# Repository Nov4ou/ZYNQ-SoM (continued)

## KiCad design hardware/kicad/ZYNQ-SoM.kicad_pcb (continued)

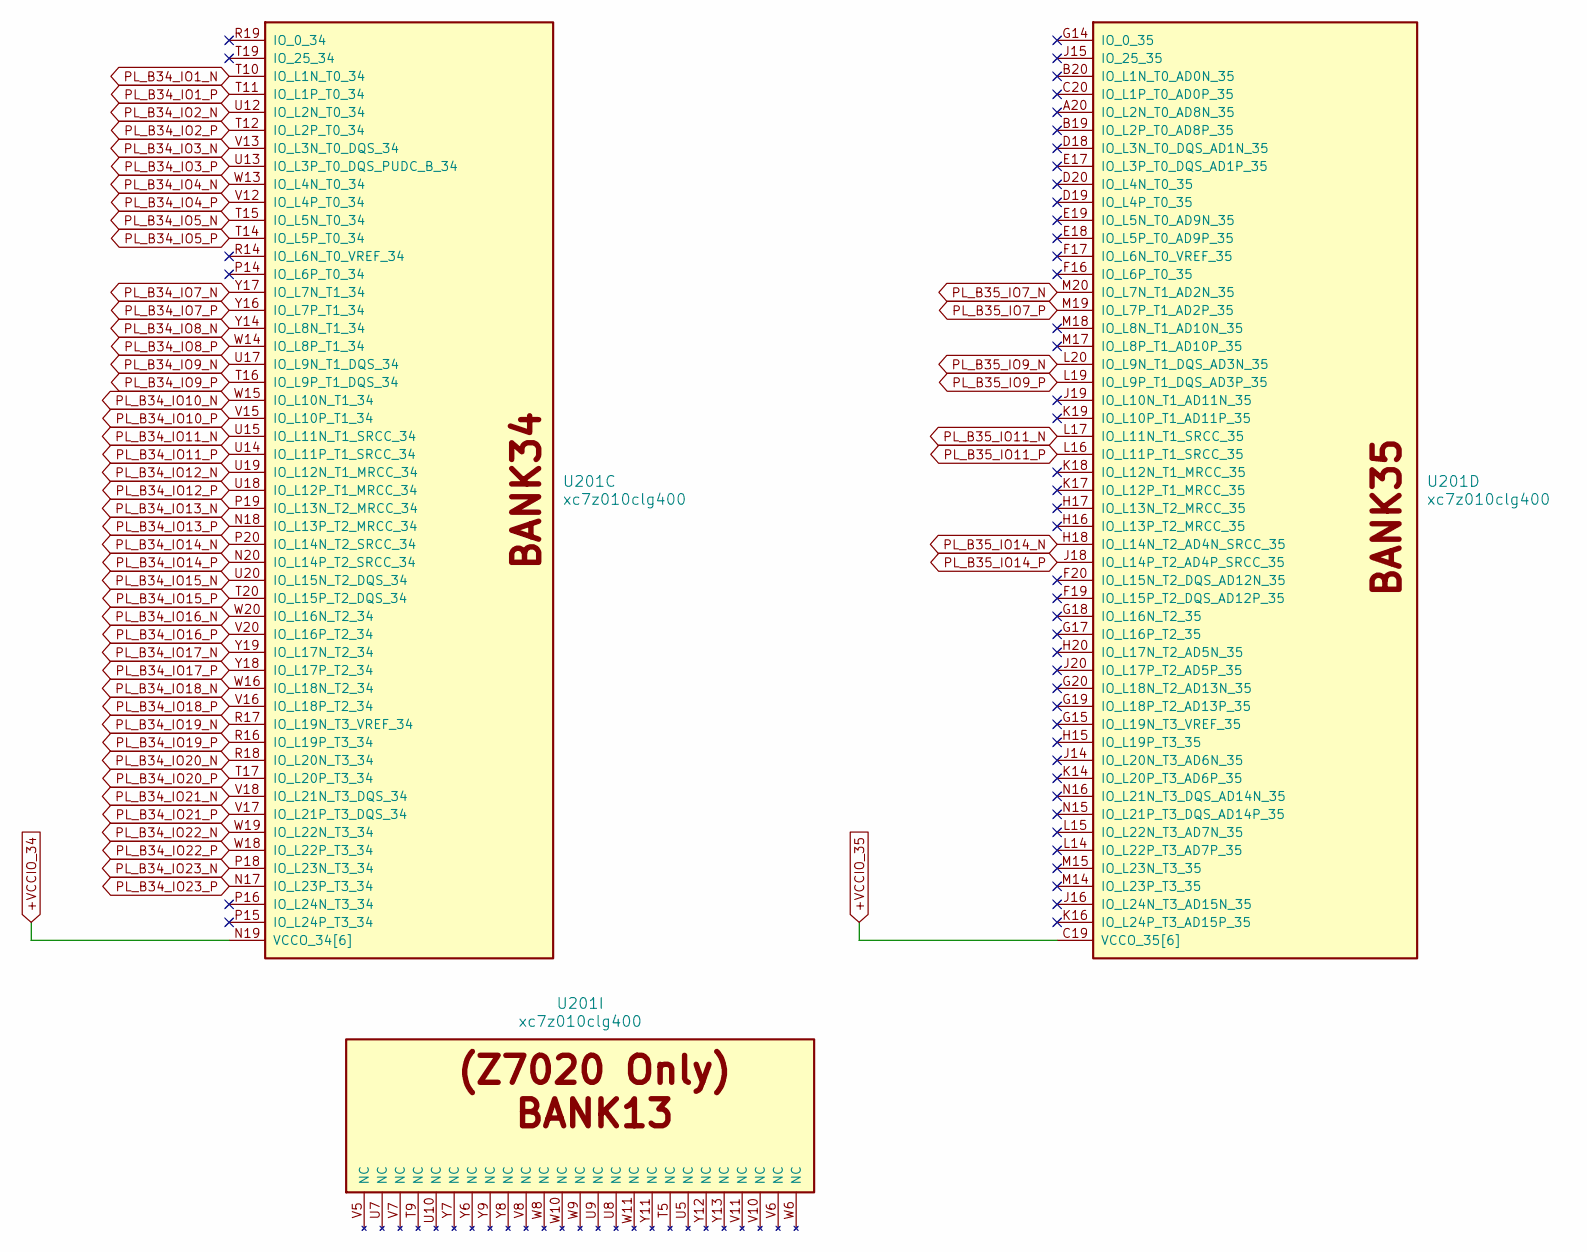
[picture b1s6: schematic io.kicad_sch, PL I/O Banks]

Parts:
U201: xc7z010clg400; Xilinx_CLG400

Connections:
+VCCIO_34: U201.N19 (VCCO_34[6]), U201.R15 (VCCO_34[6]), U201.T18 (VCCO_34[6]), U201.V14 (VCCO_34[6]), U201.W17 (VCCO_34[6]), U201.Y20 (VCCO_34[6]); also elsewhere on the board
+VCCIO_35: U201.C19 (VCCO_35[6]), U201.F18 (VCCO_35[6]), U201.H14 (VCCO_35[6]), U201.J17 (VCCO_35[6]), U201.K20 (VCCO_35[6]), U201.M16 (VCCO_35[6]); also elsewhere on the board
PL_B34_IO1_N: U201.T10 (IO_L1N_T0_34); also elsewhere on the board
PL_B34_IO1_P: U201.T11 (IO_L1P_T0_34); also elsewhere on the board
PL_B34_IO2_N: U201.U12 (IO_L2N_T0_34); also elsewhere on the board
PL_B34_IO2_P: U201.T12 (IO_L2P_T0_34); also elsewhere on the board
PL_B34_IO3_N: U201.V13 (IO_L3N_T0_DQS_34); also elsewhere on the board
PL_B34_IO3_P: U201.U13 (IO_L3P_T0_DQS_PUDC_B_34); also elsewhere on the board
PL_B34_IO4_N: U201.W13 (IO_L4N_T0_34); also elsewhere on the board
PL_B34_IO4_P: U201.V12 (IO_L4P_T0_34); also elsewhere on the board
PL_B34_IO5_N: U201.T15 (IO_L5N_T0_34); also elsewhere on the board
PL_B34_IO5_P: U201.T14 (IO_L5P_T0_34); also elsewhere on the board
PL_B34_IO7_N: U201.Y17 (IO_L7N_T1_34); also elsewhere on the board
PL_B34_IO7_P: U201.Y16 (IO_L7P_T1_34); also elsewhere on the board
PL_B34_IO8_N: U201.Y14 (IO_L8N_T1_34); also elsewhere on the board
PL_B34_IO8_P: U201.W14 (IO_L8P_T1_34); also elsewhere on the board
PL_B34_IO9_N: U201.U17 (IO_L9N_T1_DQS_34); also elsewhere on the board
PL_B34_IO9_P: U201.T16 (IO_L9P_T1_DQS_34); also elsewhere on the board
PL_B34_IO10_N: U201.W15 (IO_L10N_T1_34); also elsewhere on the board
PL_B34_IO10_P: U201.V15 (IO_L10P_T1_34); also elsewhere on the board
PL_B34_IO11_N: U201.U15 (IO_L11N_T1_SRCC_34); also elsewhere on the board
PL_B34_IO11_P: U201.U14 (IO_L11P_T1_SRCC_34); also elsewhere on the board
PL_B34_IO12_N: U201.U19 (IO_L12N_T1_MRCC_34); also elsewhere on the board
PL_B34_IO12_P: U201.U18 (IO_L12P_T1_MRCC_34); also elsewhere on the board
PL_B34_IO13_N: U201.P19 (IO_L13N_T2_MRCC_34); also elsewhere on the board
PL_B34_IO13_P: U201.N18 (IO_L13P_T2_MRCC_34); also elsewhere on the board
PL_B34_IO14_N: U201.P20 (IO_L14N_T2_SRCC_34); also elsewhere on the board
PL_B34_IO14_P: U201.N20 (IO_L14P_T2_SRCC_34); also elsewhere on the board
PL_B34_IO15_N: U201.U20 (IO_L15N_T2_DQS_34); also elsewhere on the board
PL_B34_IO15_P: U201.T20 (IO_L15P_T2_DQS_34); also elsewhere on the board
PL_B34_IO16_N: U201.W20 (IO_L16N_T2_34); also elsewhere on the board
PL_B34_IO16_P: U201.V20 (IO_L16P_T2_34); also elsewhere on the board
PL_B34_IO17_N: U201.Y19 (IO_L17N_T2_34); also elsewhere on the board
PL_B34_IO17_P: U201.Y18 (IO_L17P_T2_34); also elsewhere on the board
PL_B34_IO18_N: U201.W16 (IO_L18N_T2_34); also elsewhere on the board
PL_B34_IO18_P: U201.V16 (IO_L18P_T2_34); also elsewhere on the board
PL_B34_IO19_N: U201.R17 (IO_L19N_T3_VREF_34); also elsewhere on the board
PL_B34_IO19_P: U201.R16 (IO_L19P_T3_34); also elsewhere on the board
PL_B34_IO20_N: U201.R18 (IO_L20N_T3_34); also elsewhere on the board
PL_B34_IO20_P: U201.T17 (IO_L20P_T3_34); also elsewhere on the board
PL_B34_IO21_N: U201.V18 (IO_L21N_T3_DQS_34); also elsewhere on the board
PL_B34_IO21_P: U201.V17 (IO_L21P_T3_DQS_34); also elsewhere on the board
PL_B34_IO22_N: U201.W19 (IO_L22N_T3_34); also elsewhere on the board
PL_B34_IO22_P: U201.W18 (IO_L22P_T3_34); also elsewhere on the board
PL_B34_IO23_N: U201.P18 (IO_L23N_T3_34); also elsewhere on the board
PL_B34_IO23_P: U201.N17 (IO_L23P_T3_34); also elsewhere on the board
PL_B35_IO7_N: U201.M20 (IO_L7N_T1_AD2N_35); also elsewhere on the board
PL_B35_IO7_P: U201.M19 (IO_L7P_T1_AD2P_35); also elsewhere on the board
PL_B35_IO9_N: U201.L20 (IO_L9N_T1_DQS_AD3N_35); also elsewhere on the board
PL_B35_IO9_P: U201.L19 (IO_L9P_T1_DQS_AD3P_35); also elsewhere on the board
PL_B35_IO11_N: U201.L17 (IO_L11N_T1_SRCC_35); also elsewhere on the board
PL_B35_IO11_P: U201.L16 (IO_L11P_T1_SRCC_35); also elsewhere on the board
PL_B35_IO14_N: U201.H18 (IO_L14N_T2_AD4N_SRCC_35); also elsewhere on the board
PL_B35_IO14_P: U201.J18 (IO_L14P_T2_AD4P_SRCC_35); also elsewhere on the board

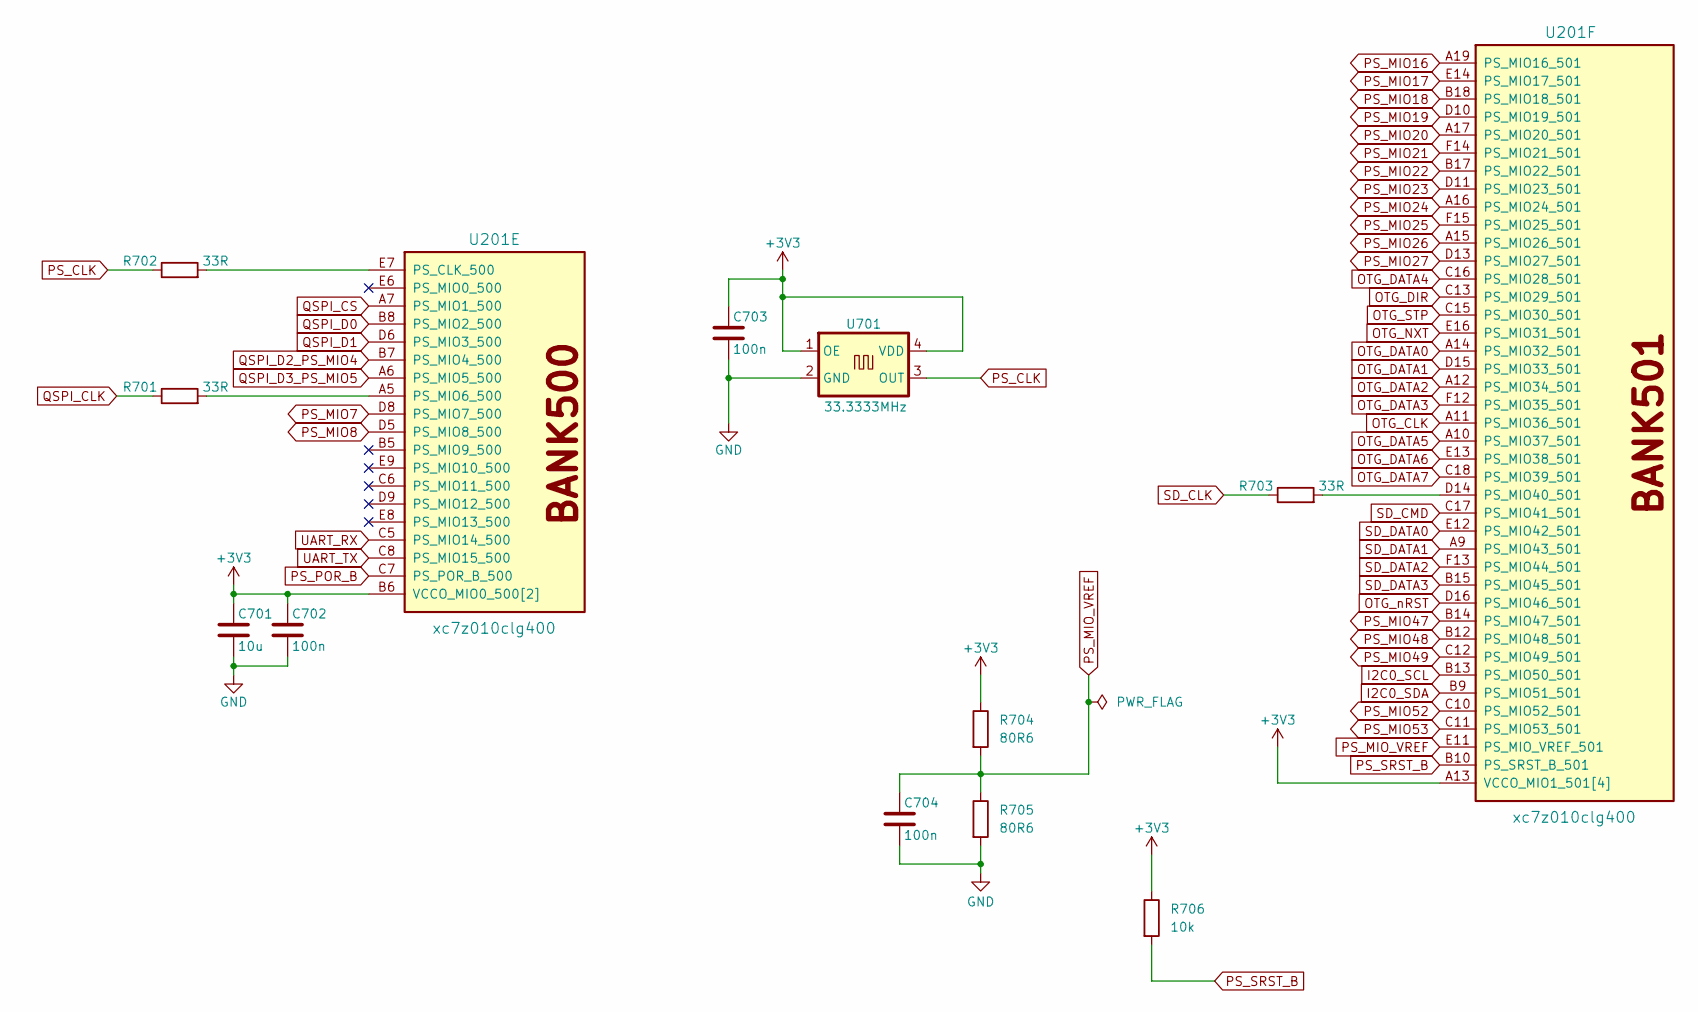
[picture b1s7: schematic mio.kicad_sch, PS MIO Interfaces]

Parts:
C701: 10u; C_0805_2012Metric
C702, C703, C704: 100n; C_0402_1005Metric
R701, R702, R703: 33R; R_0402_1005Metric
R704, R705: 80R6; R_0402_1005Metric
R706: 10k; R_0402_1005Metric
U201: xc7z010clg400; Xilinx_CLG400
U701: 33.3333MHz; Oscillator_SMD_SeikoEpson_SG8002CE-4Pin_3.2x2.5mm

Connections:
+3V3: C701.1, C702.1, C703.1, R704.1, R706.1, U201.A13 (VCCO_MIO1_501[4]), U201.B6 (VCCO_MIO0_500[2]), U201.B16 (VCCO_MIO1_501[4]), U201.D7 (VCCO_MIO0_500[2]), U201.D12 (VCCO_MIO1_501[4]), U201.E15 (VCCO_MIO1_501[4]), U701.1 (OE), U701.4 (VDD); also elsewhere on the board
GND: C701.2, C702.2, C703.2, C704.2, R705.2, U701.2 (GND); also elsewhere on the board
I2C0_SCL: U201.B13 (PS_MIO50_501); also elsewhere on the board
I2C0_SDA: U201.B9 (PS_MIO51_501); also elsewhere on the board
unnamed: R702.2, U201.E7 (PS_CLK_500)
unnamed: R701.2, U201.A5 (PS_MIO6_500)
unnamed: R703.2, U201.D14 (PS_MIO40_501)
OTG_CLK: U201.A11 (PS_MIO36_501); also elsewhere on the board
OTG_DATA0: U201.A14 (PS_MIO32_501); also elsewhere on the board
OTG_DATA1: U201.D15 (PS_MIO33_501); also elsewhere on the board
OTG_DATA2: U201.A12 (PS_MIO34_501); also elsewhere on the board
OTG_DATA3: U201.F12 (PS_MIO35_501); also elsewhere on the board
OTG_DATA4: U201.C16 (PS_MIO28_501); also elsewhere on the board
OTG_DATA5: U201.A10 (PS_MIO37_501); also elsewhere on the board
OTG_DATA6: U201.E13 (PS_MIO38_501); also elsewhere on the board
OTG_DATA7: U201.C18 (PS_MIO39_501); also elsewhere on the board
OTG_DIR: U201.C13 (PS_MIO29_501); also elsewhere on the board
OTG_NXT: U201.E16 (PS_MIO31_501); also elsewhere on the board
OTG_STP: U201.C15 (PS_MIO30_501); also elsewhere on the board
OTG_nRST: U201.D16 (PS_MIO46_501); also elsewhere on the board
PS_CLK: R702.1, U701.3 (OUT)
PS_MIO7: U201.D8 (PS_MIO7_500); also elsewhere on the board
PS_MIO8: U201.D5 (PS_MIO8_500); also elsewhere on the board
PS_MIO16: U201.A19 (PS_MIO16_501); also elsewhere on the board
PS_MIO17: U201.E14 (PS_MIO17_501); also elsewhere on the board
PS_MIO18: U201.B18 (PS_MIO18_501); also elsewhere on the board
PS_MIO19: U201.D10 (PS_MIO19_501); also elsewhere on the board
PS_MIO20: U201.A17 (PS_MIO20_501); also elsewhere on the board
PS_MIO21: U201.F14 (PS_MIO21_501); also elsewhere on the board
PS_MIO22: U201.B17 (PS_MIO22_501); also elsewhere on the board
PS_MIO23: U201.D11 (PS_MIO23_501); also elsewhere on the board
PS_MIO24: U201.A16 (PS_MIO24_501); also elsewhere on the board
PS_MIO25: U201.F15 (PS_MIO25_501); also elsewhere on the board
PS_MIO26: U201.A15 (PS_MIO26_501); also elsewhere on the board
PS_MIO27: U201.D13 (PS_MIO27_501); also elsewhere on the board
PS_MIO47: U201.B14 (PS_MIO47_501); also elsewhere on the board
PS_MIO48: U201.B12 (PS_MIO48_501); also elsewhere on the board
PS_MIO49: U201.C12 (PS_MIO49_501); also elsewhere on the board
PS_MIO52: U201.C10 (PS_MIO52_501); also elsewhere on the board
PS_MIO53: U201.C11 (PS_MIO53_501); also elsewhere on the board
PS_MIO_VREF: C704.1, R704.2, R705.1, U201.E11 (PS_MIO_VREF_501)
PS_POR_B: U201.C7 (PS_POR_B_500); also elsewhere on the board
PS_SRST_B: R706.2, U201.B10 (PS_SRST_B_501)
QSPI_CLK: R701.1; also elsewhere on the board
QSPI_CS: U201.A7 (PS_MIO1_500); also elsewhere on the board
QSPI_D0: U201.B8 (PS_MIO2_500); also elsewhere on the board
QSPI_D1: U201.D6 (PS_MIO3_500); also elsewhere on the board
QSPI_D2_PS_MIO4: U201.B7 (PS_MIO4_500); also elsewhere on the board
QSPI_D3_PS_MIO5: U201.A6 (PS_MIO5_500); also elsewhere on the board
SD_CLK: R703.1; also elsewhere on the board
SD_CMD: U201.C17 (PS_MIO41_501); also elsewhere on the board
SD_DATA0: U201.E12 (PS_MIO42_501); also elsewhere on the board
SD_DATA1: U201.A9 (PS_MIO43_501); also elsewhere on the board
SD_DATA2: U201.F13 (PS_MIO44_501); also elsewhere on the board
SD_DATA3: U201.B15 (PS_MIO45_501); also elsewhere on the board
UART_RX: U201.C5 (PS_MIO14_500); also elsewhere on the board
UART_TX: U201.C8 (PS_MIO15_500); also elsewhere on the board

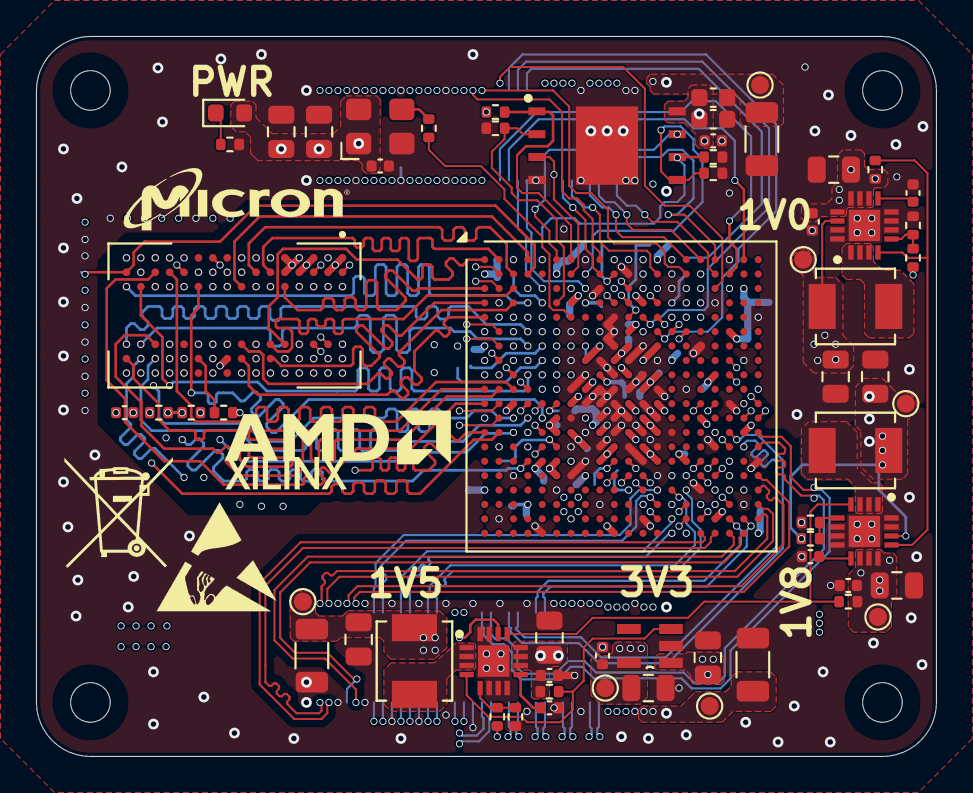
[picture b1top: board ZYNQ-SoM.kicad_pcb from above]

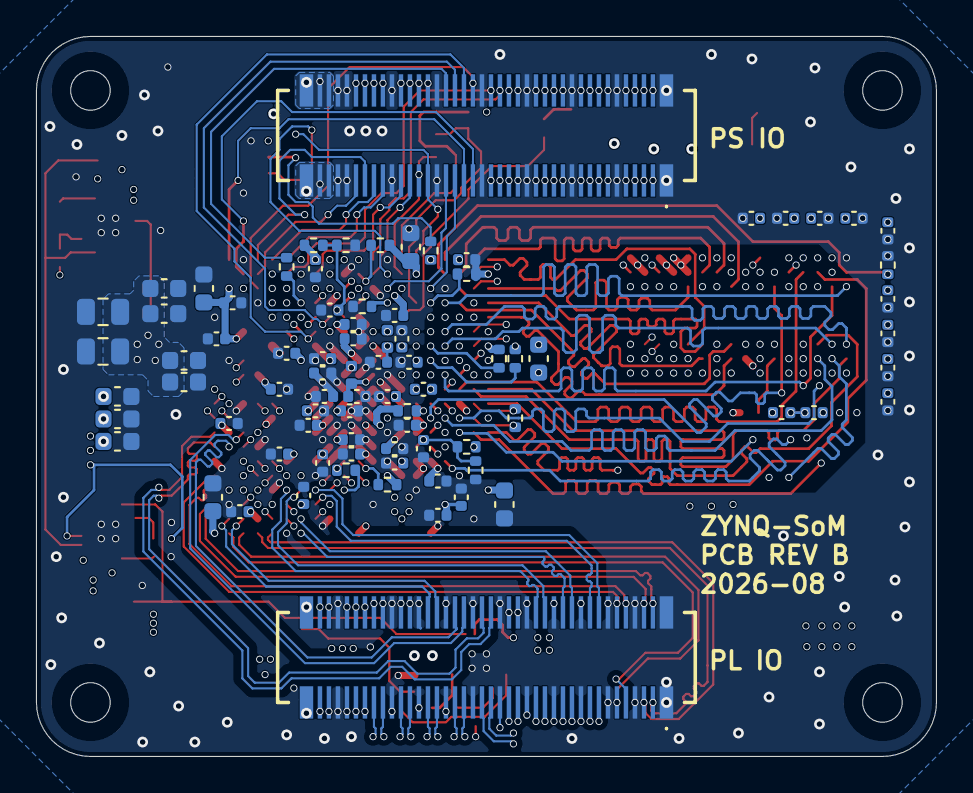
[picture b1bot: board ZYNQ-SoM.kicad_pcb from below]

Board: 6 copper layers, 50.0 x 40.0 mm, 147 parts (81 on the bottom side), 191 nets.

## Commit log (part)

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2026-06-07 Init commit
2026-06-07 feat: finish ddr sch design
2026-06-08 feat: finish power sch design
2026-06-08 feat: continue ps mio sch design
2026-06-08 feat: continue PL sch design
2026-06-08 feat: continue improve sch design
2026-06-09 feat: basic power layout
2026-06-11 feat: finish basic ddr3 routing
2026-06-11 feat: need finish power layout
2026-06-12 layout: route mio and some io
2026-06-14 layout: continue layout pl io
